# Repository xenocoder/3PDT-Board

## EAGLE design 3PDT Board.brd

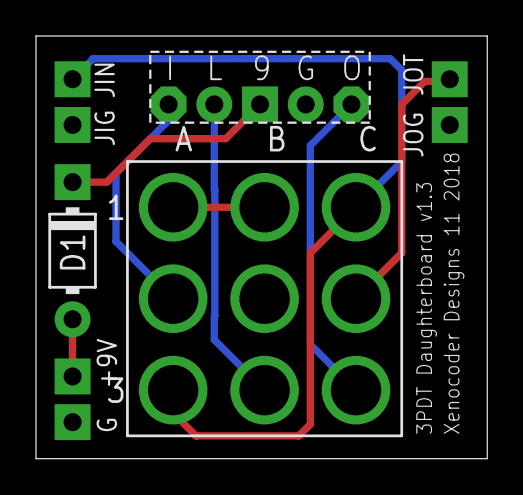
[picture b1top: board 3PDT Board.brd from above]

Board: 2 copper layers, 25.1 x 23.5 mm, 9 parts (0 on the bottom side), 9 nets.

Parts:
+9V: +9V(T); SQUARE
D1: DO41-3
G: GND(T); SQUARE
JIG: GND(T); SQUARE
JIN: SQUARE
JOG: GND(T); SQUARE
JOT: SQUARE
SW2: 3PDT
U$1: BOARDLINK

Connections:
+9V: +9V.1, D1.A
GND: G.1, JIG.1, JOG.1, SW2.B2, U$1.4
unnamed: SW2.B3, U$1.2
unnamed: JOT.1, SW2.C2
unnamed: SW2.A1, SW2.B1
unnamed: JIN.1, SW2.A3, SW2.C1
unnamed: SW2.A2, U$1.1
unnamed: SW2.C3, U$1.5
unnamed: D1.C, U$1.3

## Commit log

2018-01-18 First Commit to setup master branch
2018-01-18 Fixed ground connections so jack grounds actually connect to ground!
2018-09-30 Fixed circuit and made panel
2018-10-19 Added Schematic and BOM
2018-11-24 Update to panel with fixed Diode direction
